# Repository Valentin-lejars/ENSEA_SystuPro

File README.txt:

//1 Saisie du Schéma
//1.2 Le microcontroleur sous KiCAD

13.PB9 est la pin du BOOT0. En la reliant à la masse on force le BOOT0 à 0

14. Les composants L1, C5 et C7 ont pour but de filtrer l'alimentation pour la rendre propre pour les autres composants.

//1.3 Le reste du schéma

3. les valeurs des condensateurs (1µF) sont indiqués à la page 3/17 de la datasheet du BU33SD5WG-TR.

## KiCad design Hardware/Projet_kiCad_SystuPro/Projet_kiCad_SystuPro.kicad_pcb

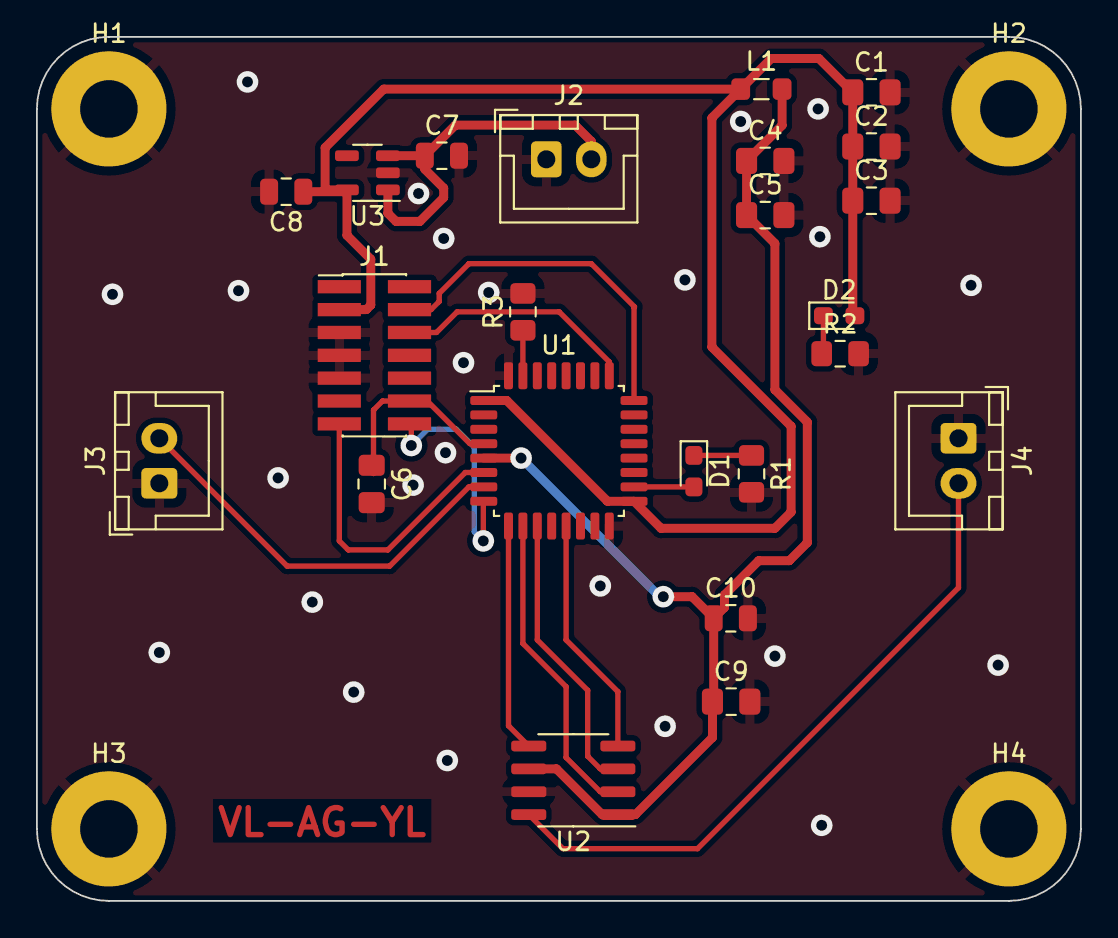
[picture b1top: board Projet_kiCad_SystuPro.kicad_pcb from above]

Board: 2 copper layers, 58.0 x 48.0 mm, 27 parts (0 on the bottom side), 19 nets.

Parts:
C1: 4u7; C_0805_2012Metric_Pad1.18x1.45mm_HandSolder
C2, C3, C6, C9: 100n; C_0805_2012Metric_Pad1.18x1.45mm_HandSolder
C4: 1u; C_0805_2012Metric_Pad1.18x1.45mm_HandSolder
C5: 10n; C_0805_2012Metric_Pad1.18x1.45mm_HandSolder
C7, C8: 1uf; C_0805_2012Metric
C10: 10u; C_0805_2012Metric
D1: ORANGE TLM01100-GS8; LED_0603_1608Metric_Pad1.05x0.95mm_HandSolder
D2: GREEN LED; LED_0603_1608Metric_Pad1.05x0.95mm_HandSolder
H1, H2, H3, H4: MountingHole_Pad; MountingHole_3.2mm_M3_Pad
J1: Conn_02x07_Odd_Even; PinHeader_2x07_P1.27mm_Vertical_SMD
J2, J3, J4: Conn_01x02; JST_XH_B2B-XH-A_1x02_P2.50mm_Vertical
L1: 39n; L_0805_2012Metric_Pad1.05x1.20mm_HandSolder
R1, R2: 1k; L_0805_2012Metric_Pad1.15x1.40mm_HandSolder
R3: 100k; L_0805_2012Metric_Pad1.15x1.40mm_HandSolder
U1: STM32L021K4Tx; LQFP-32_7x7mm_P0.8mm
U2: MCP4801; SOIC-8_3.9x4.9mm_P1.27mm
U3: LDO BU33SD5WG-TR; SOT-23-5

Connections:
+3.3V: C1.1, C2.1, C3.1, C8.1, D2.2 (A), J1.3, L1.1, U1.1 (VDD), U1.17 (VDD), U3.5 (VOUT)
+3.3VA: C4.1, C5.1, C9.1, C10.1, L1.2, U1.5 (VDDA), U2.1 (Vdd), U2.6 (~SHDN)
+5V: C7.1, J2.2, U3.1 (VIN), U3.3 (~SHDN)
/ADC_IN1: J3.2, U1.7 (PA1)
/DAC_OUT: J4.2, U2.8 (Vout)
/DAC_nCS: U1.10 (PA4), U2.2 (~CS)
/DAC_nLDAC: U1.9 (PA3), U2.5 (~LDAC)
/LED_STATUS: D1.2 (A), U1.18 (PA8)
/NRST: C6.1, J1.12, U1.4 (NRST)
/SPI1_MOSI: U1.13 (PA7), U2.4 (SDI)
/SPI1_SCK: U1.11 (PA5), U2.3 (SCK)
/SWDCK: J1.6, U1.25 (PA15)
/SWDIO: J1.4, U1.24 (PA14)
/USART2_RX: J1.13, U1.6 (PA0)
/USART2_TX: J1.14, U1.8 (PA2)
GND: C1.2, C2.2, C3.2, C4.2, C5.2, C6.2, C7.2, C8.2, C9.2, C10.2, H1.1, H2.1, H3.1, H4.1, J1.5, J1.7, J1.9, J2.1, J3.1, J4.1, R1.2, R2.2, R3.2, U1.16 (VSS), U1.32 (VSS), U2.7 (Vss), U3.2 (GND)
unnamed: D1.1 (K), R1.1
unnamed: D2.1 (K), R2.1
unnamed: R3.1, U1.31 (PB9)

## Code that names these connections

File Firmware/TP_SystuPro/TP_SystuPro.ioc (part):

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Mcu.Name=STM32L021K4Tx
Mcu.Package=LQFP32
Mcu.UserName=STM32L021K4Tx
PA0-CK_IN.Mode=Asynchronous
PA0-CK_IN.Signal=USART2_RX
PA1.Mode=IN1
PA1.Signal=ADC_IN1
PA13.Mode=Serial_Wire
PA13.Signal=SYS_SWDIO
PA14.Mode=Serial_Wire
PA14.Signal=SYS_SWCLK
PA2.Mode=Asynchronous
PA2.Signal=USART2_TX
PA3.GPIOParameters=GPIO_Label
PA3.GPIO_Label=DAC_nLDAC
PA3.Signal=GPIO_Input
PA4.GPIOParameters=GPIO_Label
PA4.GPIO_Label=DAC_nCS
PA4.Signal=GPIO_Input
PA5.GPIOParameters=GPIO_Label
PA5.GPIO_Label=SP1_SCK
PA5.Signal=GPIO_Input
PA6.Mode=Full_Duplex_Master
PA6.Signal=SPI1_MISO
PA7.Mode=Full_Duplex_Master
PA7.Signal=SPI1_MOSI
PA8.Signal=S_TIM2_CH1
PB3.Mode=Full_Duplex_Master
PB3.Signal=SPI1_SCK
RCC.HSE_VALUE=8000000
RCC.SYSCLKFreq_VALUE=32000000
RCC.SYSCLKSource=RCC_SYSCLKSOURCE_PLLCLK
board=custom

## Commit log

2024-02-09 Datashhets
2024-02-09 StmCubeProject
2024-02-09 Fin de séance
2024-02-29 Shematic et PCB Updated
2024-03-14 HW update
2024-03-14 creation readme
2024-03-14 Firware_L432
